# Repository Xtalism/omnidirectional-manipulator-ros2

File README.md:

# Omnidirectional Manipulator Robot using ROS2

Omnidirectional Manipulator Robot using ROS2 and MicroROS.

## Table of Contents
- [Omnidirectional Manipulator Robot using ROS2](#omnidirectional-manipulator-robot-using-ros2)
  - [Table of Contents](#table-of-contents)
  - [Current Simulation Results](#current-simulation-results)
  - [Hardware Requirements](#hardware-requirements)
  - [Software Requirements](#software-requirements)
  - [Installation](#installation)
  - [Controller Setup](#controller-setup)
  - [Project Setup](#project-setup)

## Current Simulation Results

[Check the project on youtube](https://youtube.com/playlist?list=PL3C8yCOARHROVQ0J0LYWpv6aPSOsDYQEf&feature=shared) 

## Hardware Requirements
- ESP32.
- JGB37-520 motors.
- H bridge L293D.
- Xbox controller.
- 18650 batteries.
- Raspberry Pi 5 (4gb RAM).
- Arduino Mega 2560.
- MG995 servomotors.
- Intel Realsense D415.
- Lidar Sensor LD19 (LDROBOT).

## Software Requirements
In order for the project to work we need to have installed [Ubuntu 24.04 LTS Noble Numbat](https://releases.ubuntu.com/noble/) alocated
in a partition with a Windows dual boot or as the main Operating System of your machine. 

You can try to virtualize it but in my experience, networking and driver problems arouse.

## Installation
We need to install [ROS Jazzy](https://wiki.ros.org/jazzy), you can follow the [documentation](https://docs.ros.org/en/jazzy/Installation/Ubuntu-Install-Debs.html) on how to install it or you can follow and run these few commands inside Ubuntu's terminal:

```bash
sudo apt update && sudo apt install locales
sudo locale-gen en_US en_US.UTF-8
sudo update-locale LC_ALL=en_US.UTF-8 LANG=en_US.UTF-8
export LANG=en_US.UTF-8
```

```bash
sudo apt install software-properties-common
sudo add-apt-repository universe
```

```bash
sudo apt update && sudo apt install curl -y
sudo curl -sSL https://raw.githubusercontent.com/ros/rosdistro/master/ros.key -o /usr/share/keyrings/ros-archive-keyring.gpg
echo "deb [arch=$(dpkg --print-architecture) signed-by=/usr/share/keyrings/ros-archive-keyring.gpg] http://packages.ros.org/ros2/ubuntu $(. /etc/os-release && echo $UBUNTU_CODENAME) main" | sudo tee /etc/apt/sources.list.d/ros2.list > /dev/null
```

```bash
sudo apt update && sudo apt install ros-dev-tools
sudo apt update
sudo apt upgrade
sudo apt install ros-jazzy-desktop
```

## Controller Setup
You can use any controller listed in the [documentation](http://wiki.ros.org/joy). I'm personally
using an 8bitdo Ultimate C 2.4GHz. It is not a Xbox Controller per se but I managed to find some drivers to 
trick Linux into thinking it is a generic Xbox Controller ([you can find the post here](https://gist.github.com/ammuench/0dcf14faf4e3b000020992612a2711e2)):

```bash
touch /etc/udev/rules.d/99-8bitdo-xinput.rules
sudo nano /etc/udev/rules.d/99-8bitdo-xinput.rules
```
Inside 99-8bitdo-xinput.rules you type the following and save:
```bash
ACTION=="add", ATTRS{idVendor}=="2dc8", ATTRS{idProduct}=="3106", RUN+="/sbin/modprobe xpad", RUN+="/bin/sh -c 'echo 2dc8 3106 > /sys/bus/usb/drivers/xpad/new_id'"
```

Reload udevadm service
```bash
sudo udevadm control --reload
```

You also need to make your [joystick device accesible](http://wiki.ros.org/joy/Tutorials/ConfiguringALinuxJoystick):

```bash
ls -l /dev/input/jsX
```

You will see something similar to:
```bash
crw-rw-XX- 1 root dialout 188, 0 2009-08-14 12:04 /dev/input/jsX
```

We need to change XX to rw:
```bash
sudo chmod a+rw /dev/input/jsX
```

## Project Setup

Clone this repository:

```bash
git clone https://github.com/Xtalism/ROS2-Omni-Manipulator.git
```

We need to source, install dependencies and compile our workspace just as follows:

Sourcing ROS2:
```bash
source /opt/ros/${ROS_DISTRO}/setup.bash
```

Sourcing the project:
```bash
cd ros2_ws/
source install/setup.bash
```
Installing dependencies and compiling the project:
```bash
rosdep install --from-paths src --ignore-src -r -y
colcon build --symlink-install
```

To run any package or launch file"

```bash
ros2 run <package_name> <program_name>
ros2 launch <package_name> <launch_file>
```

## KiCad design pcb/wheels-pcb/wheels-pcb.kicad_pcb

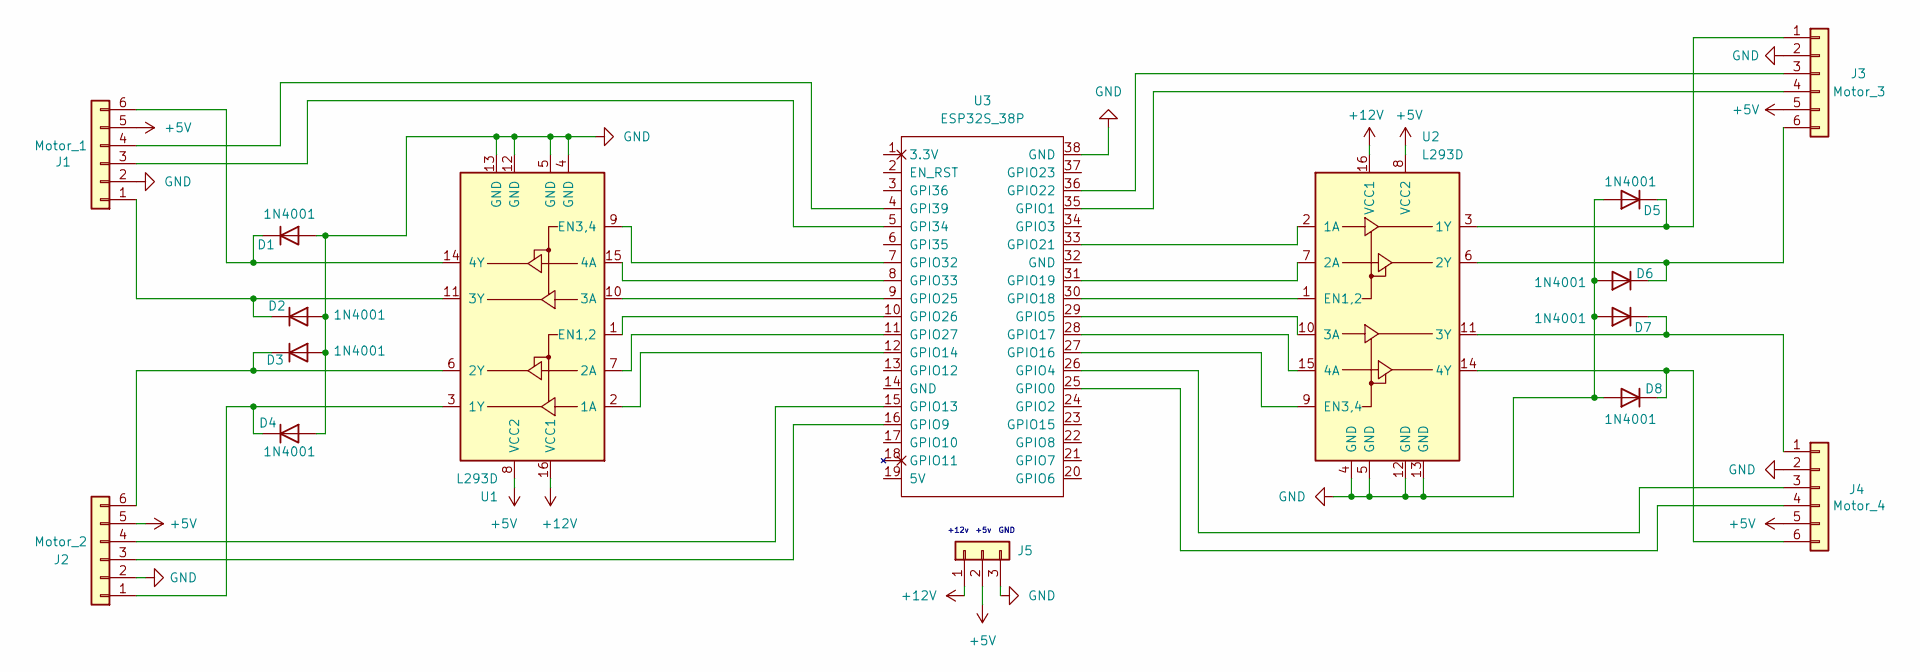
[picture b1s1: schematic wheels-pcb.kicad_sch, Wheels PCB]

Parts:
D1, D2, D3, D4, D5, D6, D7, D8: 1N4001; D_DO-41_SOD81_P10.16mm_Horizontal
J1: Motor_1; JST_EH_B6B-EH-A_1x06_P2.50mm_Vertical
J2: Motor_2; JST_EH_B6B-EH-A_1x06_P2.50mm_Vertical
J3: Motor_3; JST_EH_B6B-EH-A_1x06_P2.50mm_Vertical
J4: Motor_4; JST_EH_B6B-EH-A_1x06_P2.50mm_Vertical
J5: Conn_01x03; JST_EH_S3B-EH_1x03_P2.50mm_Horizontal
U1, U2: L293D; DIP-16_W7.62mm
U3: ESP32S_38P

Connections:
+5V: J1.5, J2.5, J3.5, J4.5, J5.2, U1.8 (VCC2), U2.8 (VCC2)
+12V: J5.1, U1.16 (VCC1), U2.16 (VCC1)
GND: D1.2 (A), D2.2 (A), D3.2 (A), D4.2 (A), D5.2 (A), D6.2 (A), D7.2 (A), D8.2 (A), J1.2, J2.2, J3.2, J4.2, J5.3, U1.4 (GND), U1.5 (GND), U1.12 (GND), U1.13 (GND), U2.4 (GND), U2.5 (GND), U2.12 (GND), U2.13 (GND), U3.38 (GND)
unnamed: D1.1 (K), J1.6, U1.14 (4Y)
unnamed: D2.1 (K), J1.1, U1.11 (3Y)
unnamed: D3.1 (K), J2.6, U1.6 (2Y)
unnamed: D4.1 (K), J2.1, U1.3 (1Y)
unnamed: D5.1 (K), J3.1, U2.3 (1Y)
unnamed: D6.1 (K), J3.6, U2.6 (2Y)
unnamed: D7.1 (K), J4.1, U2.11 (3Y)
unnamed: D8.1 (K), J4.6, U2.14 (4Y)
unnamed: J1.3, U3.5 (GPI34)
unnamed: J1.4, U3.4 (GPI39)
unnamed: J2.3, U3.16 (GPIO9)
unnamed: J2.4, U3.15 (GPIO13)
unnamed: J3.3, U3.36 (GPIO22)
unnamed: J3.4, U3.35 (GPIO1)
unnamed: J4.3, U3.26 (GPIO4)
unnamed: J4.4, U3.25 (GPIO0)
unnamed: U1.2 (1A), U3.12 (GPIO14)
unnamed: U1.7 (2A), U3.11 (GPIO27)
unnamed: U1.10 (3A), U3.9 (GPIO25)
unnamed: U1.15 (4A), U3.8 (GPIO33)
unnamed: U1.1 (EN1,2), U3.10 (GPIO26)
unnamed: U1.9 (EN3,4), U3.7 (GPIO32)
unnamed: U2.2 (1A), U3.33 (GPIO21)
unnamed: U2.7 (2A), U3.31 (GPIO19)
unnamed: U2.10 (3A), U3.29 (GPIO5)
unnamed: U2.15 (4A), U3.28 (GPIO17)
unnamed: U2.1 (EN1,2), U3.30 (GPIO18)
unnamed: U2.9 (EN3,4), U3.27 (GPIO16)

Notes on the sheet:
+12v
GND
+5v

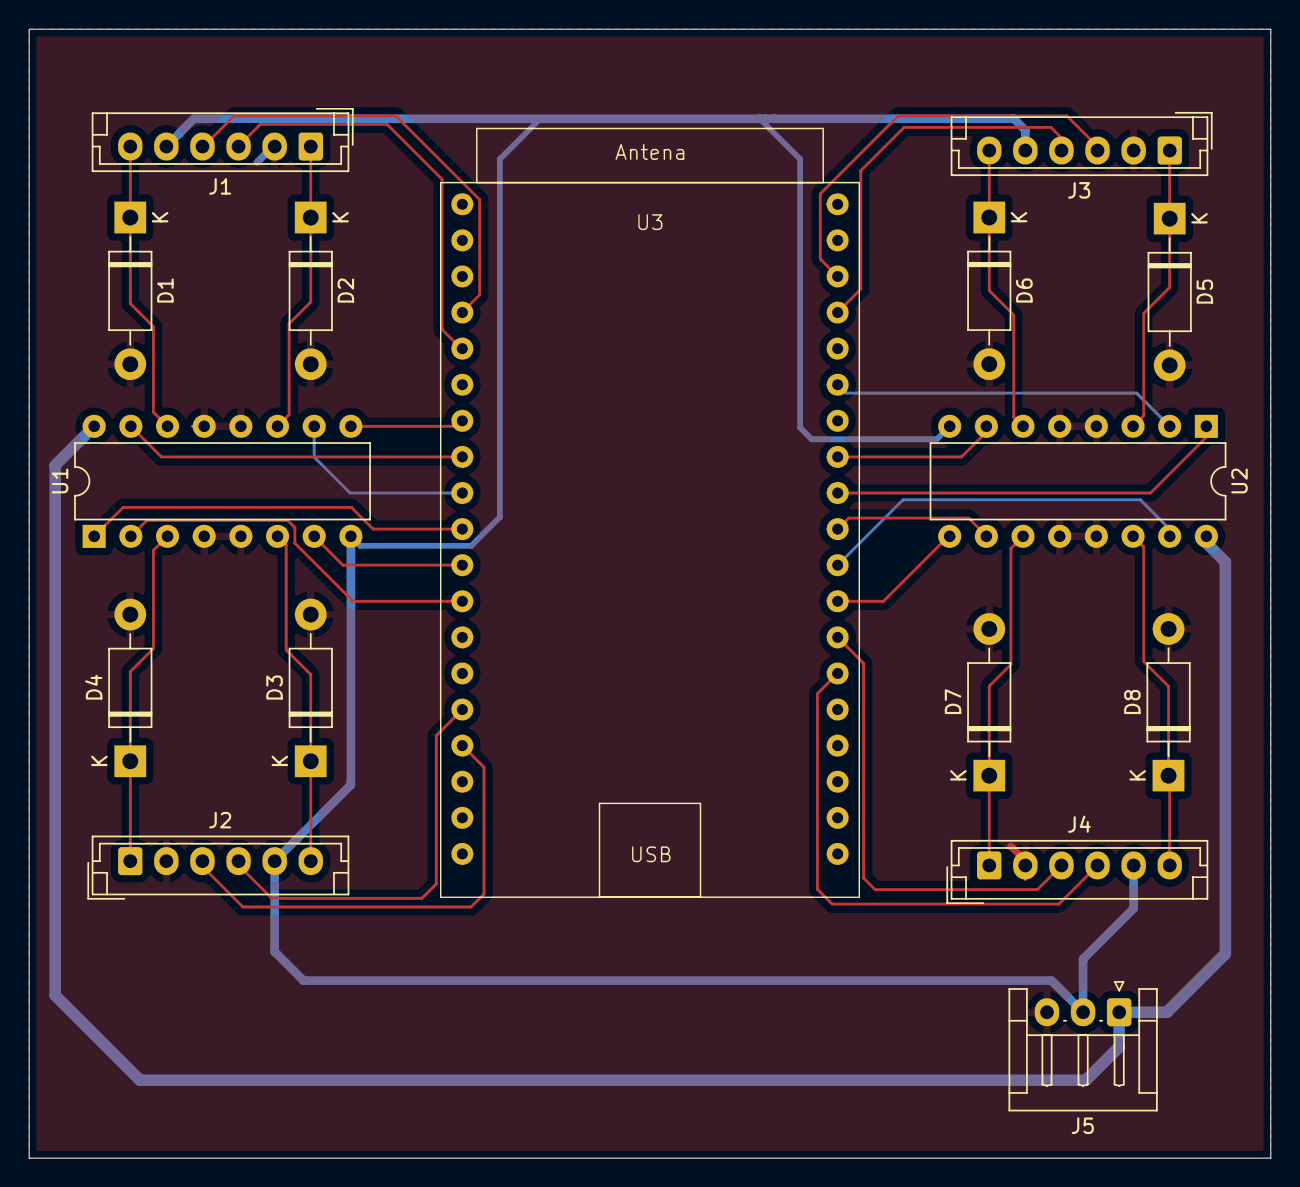
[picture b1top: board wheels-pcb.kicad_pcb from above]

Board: 2 copper layers, 86.0 x 78.2 mm, 16 parts (0 on the bottom side), 31 nets.

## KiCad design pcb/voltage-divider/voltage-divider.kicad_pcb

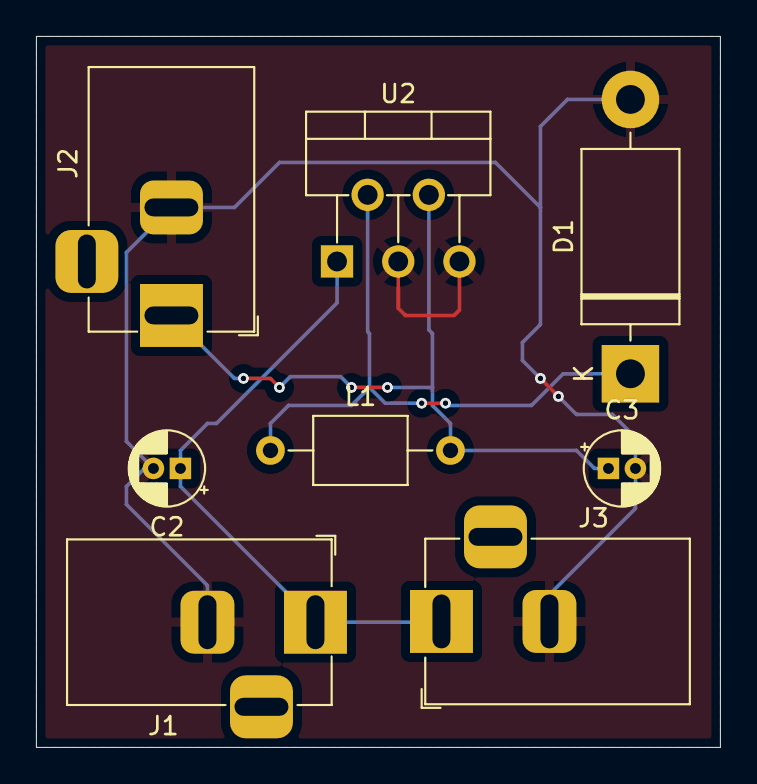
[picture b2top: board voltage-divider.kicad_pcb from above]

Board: 2 copper layers, 38.0 x 39.5 mm, 8 parts (0 on the bottom side), 4 nets.

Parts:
C2, C3: C_Small_US; CP_Radial_D4.0mm_P1.50mm
D1: 1N5821; D_DO-201AD_P15.24mm_Horizontal
J1, J2, J3: Jack-DC; BarrelJack_Horizontal
L1: L; L_Axial_L5.0mm_D3.6mm_P10.00mm_Horizontal_Murata_BL01RN1A2A2
U2: LM2596T-5; TO-220-5_P3.4x3.7mm_StaggerOdd_Lead3.8mm_Vertical

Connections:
Earth: C2.2, C3.2, D1.2 (A), J1.2, J2.2, J3.2, U2.3 (GND), U2.5 (~ON/OFF)
unnamed: D1.1 (K), L1.1, U2.2 (OUT)
unnamed: C3.1, J2.1, L1.2, U2.4 (FB)
unnamed: C2.1, J1.1, J3.1, U2.1 (VIN)

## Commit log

2025-03-08 added description
2025-03-08 changed description
2025-03-08 added image
2025-03-25 camera addition
2025-03-27 added intel realsense
2025-03-28 pcb and urdf addition
2025-03-28 urdf correction
2025-03-28 render addition
2025-03-28 README.md addition
2025-03-28 README.md
2025-03-28 step deletion
2025-03-29 pcb-modification
2025-03-29 pcb edit
2025-03-29 changed image
2025-04-01 direct kinematiks addition
2025-04-01 direct kinematics addition
2025-04-01 deletion kinematics
2025-04-01 kinematics addition
2025-04-01 pcb correction
2025-04-01 URDF edit
2025-04-01 rviz2 visualization
2025-04-01 video addition
2025-04-02 blueprints addition
2025-04-02 added lidar drivers
2025-04-02 configuration in ws
2025-04-04 microros_ws addition
2025-04-04 microros_ws update
2025-04-04 micro-ros branch
2025-04-04 ldrobot update
2025-04-04 ldrobot addition
2025-04-04 build attributes deleted
2025-04-04 lidar update
2025-04-09 rviz optimization
2025-04-09 rviz launch file
2025-04-09 gazebo simulation addition
2025-04-09 gazebo update
2025-04-10 README.md edit
2025-04-10 lidar simulation addition
2025-04-10 camera simulation addition
2025-04-26 Joystick interaction addition, in order to control Robot
2025-05-03 Robot navigation package addition
2025-05-04 Navigation and localization logic addition
2025-05-07 Micro-Ros code addition (omnidirectional logic)
2025-05-08 Physical robot movement with Microros
2025-05-09 LDROBOT lidar deletion
2025-05-09 LDROBOT LD19 driver addition
2025-05-11 Manipulator Rviz2 fix and joint publish
2025-05-12 Manipulator JointController System addition
2025-05-21 Canged Micro ROS code and PCB design also
2025-05-22 Physical Camera addition and lidar node (working in gazebo pose spawning)
2025-05-22 Documentation addition
2025-05-22 Presentation addition
2025-06-21 LICENSE
2025-11-17 Render changed
2025-11-17 Removed render
2025-11-17 Added render.png
2025-11-17 Added robot_render.png
2025-11-17 Render resolution changed
2025-11-17 Added omni_render.png
